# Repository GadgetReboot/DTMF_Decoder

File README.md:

# DTMF_Decoder
MT8870 DTMF decoder for POTS phone line interfacing <BR>
<br>
This pcb allows connecting across a phone line tip and ring and when DTMF signals are present, they are decoded into 4 bit data with a data ready signal.<br>
An Arduino can then detect DTMF touch tones present on a phone line.<br>
Note: It is recommended to only connect this circuit to a phone line after it is taken off hook to keep the AC voltages low, such as audio signals and not a high voltage ring signal.<br>
This can be achieved by switching the circuit into the phone line with a relay.<br><br>
This circuit has only been tested on a simulated phone line in a workshop environment and is not guaranteed to meet official telephone line specifications.

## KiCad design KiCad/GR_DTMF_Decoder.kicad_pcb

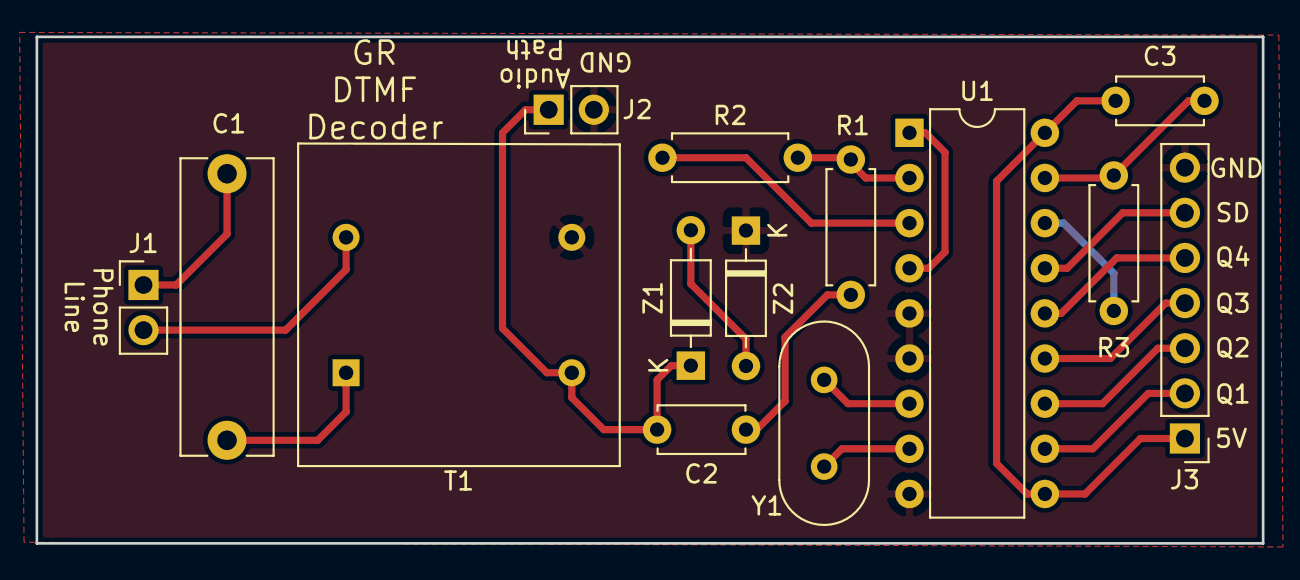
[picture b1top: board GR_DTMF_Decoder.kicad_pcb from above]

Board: 2 copper layers, 69.0 x 28.5 mm, 14 parts (0 on the bottom side), 20 nets.

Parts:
C1: 0.56uF 250V; C_Rect_L16.5mm_W5.0mm_P15.00mm_MKT
C2, C3: 100nF; C_Disc_D4.7mm_W2.5mm_P5.00mm
J1, J2: Conn_01x02; PinHeader_1x02_P2.54mm_Vertical
J3: Conn_01x07; PinHeader_1x07_P2.54mm_Vertical
R1, R2: 100K; R_Axial_DIN0207_L6.3mm_D2.5mm_P7.62mm_Horizontal
R3: 300K; R_Axial_DIN0207_L6.3mm_D2.5mm_P7.62mm_Horizontal
T1: 600:600; Transformer_NF_ETAL_P3324
U1: MT8870D; DIP-18_W7.62mm
Y1: 3.579545 MHz; Crystal_HC49-4H_Vertical
Z1, Z2: 3V3; D_DO-35_SOD27_P7.62mm_Horizontal

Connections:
+5V: C3.1, J3.1, U1.10, U1.18
/Q1: J3.2, U1.11
/Q2: J3.3, U1.12
/Q3: J3.4, U1.13
/Q4: J3.5, U1.14
/SD: J3.6, U1.15
GNDREF: J2.2, J3.7, T1.3, U1.5, U1.6, U1.9, Z2.K
unnamed: C1.1, T1.1
unnamed: C1.2, J1.1
unnamed: C2.1, R1.2
unnamed: C2.2, J2.1, T1.4, Z1.K
unnamed: C3.2, R3.1, U1.17
unnamed: J1.2, T1.2
unnamed: R1.1, R2.2, U1.2
unnamed: R2.1, U1.3
unnamed: R3.2, U1.16
unnamed: U1.1, U1.4
unnamed: U1.7, Y1.1
unnamed: U1.8, Y1.2
unnamed: Z1.A, Z2.A
